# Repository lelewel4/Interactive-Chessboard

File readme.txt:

With my collegaues, I designed PCB to interactive chessboard.

The designed board should detect a given game piece on its field and, on this basis, send data to the microcontroller.
The microcontroller processes the data and determines the possible movements.
Depending on this, the board should glow with the appropriate LED color, e.g. red - a pawn to capture.

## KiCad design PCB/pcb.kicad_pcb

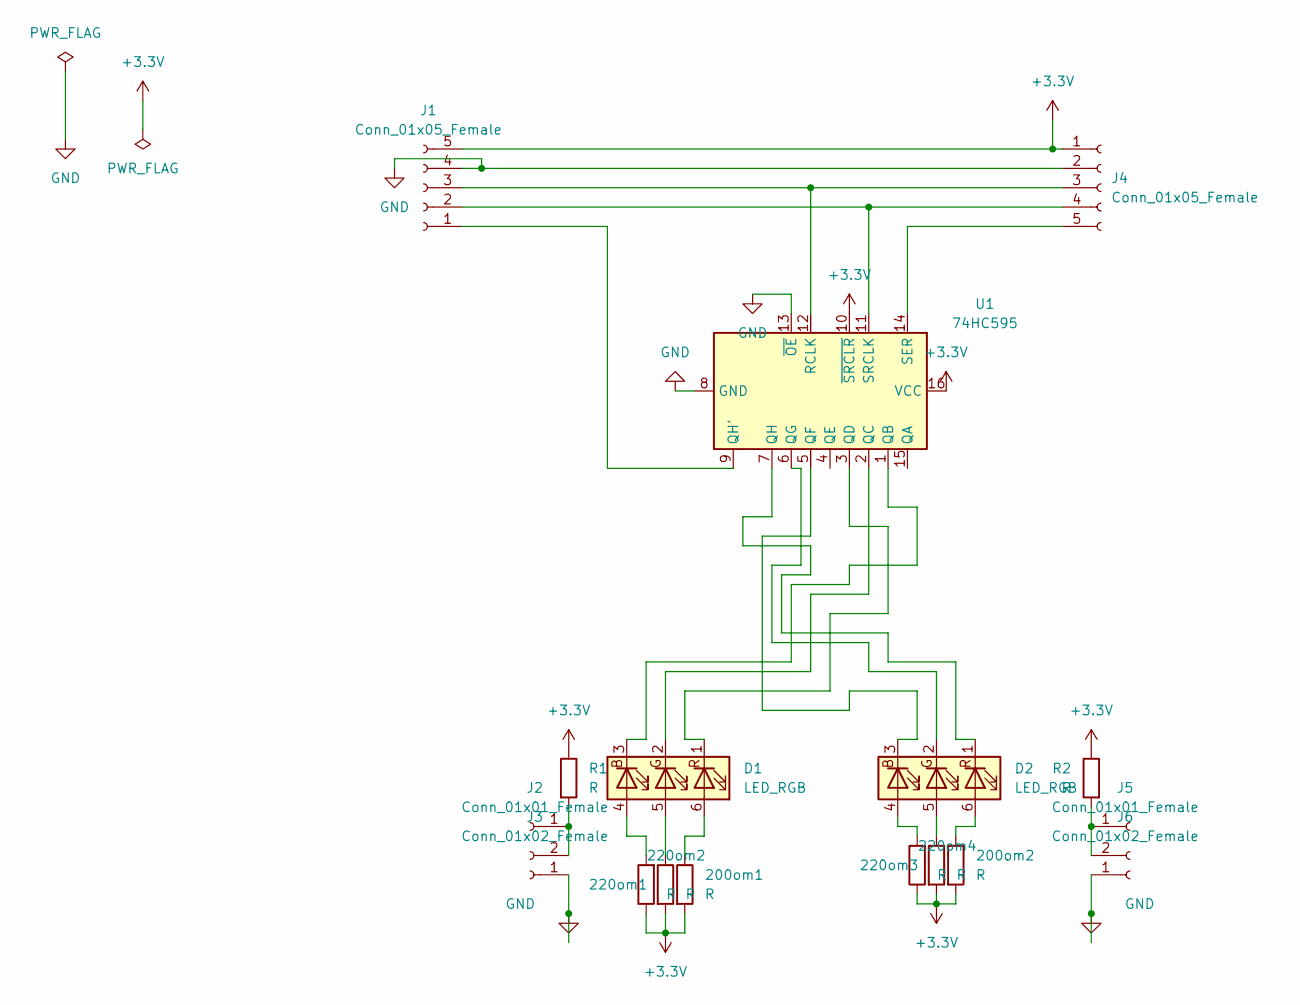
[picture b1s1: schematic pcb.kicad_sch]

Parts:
200om1, 200om2, 220om1, 220om2, 220om3, 220om4: R; R_0603_1608Metric_Pad0.98x0.95mm_HandSolder
D1, D2: LED_RGB; LED_RGB_PLCC-6
J1, J4: Conn_01x05_Female; PinHeader_1x05_P2.54mm_Vertical
J2, J5: Conn_01x01_Female; PinHeader_1x01_P2.54mm_Vertical
J3, J6: Conn_01x02_Female; PinHeader_1x02_P2.54mm_Vertical
R1, R2: R; R_0603_1608Metric_Pad0.98x0.95mm_HandSolder
U1: 74HC595; SO-16_3.9x9.9mm_P1.27mm

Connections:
+3V3: 200om1.2, 200om2.2, 220om1.1, 220om2.2, 220om3.1, 220om4.2, J1.5, J4.1, R1.1, R2.1, U1.10 (~SRCLR), U1.16 (VCC)
GND: J1.4, J3.1, J4.2, J6.1, U1.8 (GND), U1.13 (~OE)
unnamed: 200om1.1, D1.6 (RA)
unnamed: 200om2.1, D2.6 (RA)
unnamed: 220om1.2, D1.4 (BA)
unnamed: 220om2.1, D1.5 (GA)
unnamed: 220om3.2, D2.4 (BA)
unnamed: 220om4.1, D2.5 (GA)
unnamed: D2.1 (RK), U1.7 (QH)
unnamed: D2.3 (BK), U1.5 (QF)
unnamed: J1.1, U1.9 (QH')
unnamed: J1.2, J4.4, U1.11 (SRCLK)
unnamed: J1.3, J4.3, U1.12 (RCLK)
unnamed: J2.1, J3.2, R1.2
unnamed: J4.5, U1.14 (SER)
unnamed: J5.1, J6.2, R2.2
unnamed: D1.3 (BK), U1.1 (QB)
unnamed: D1.2 (GK), U1.2 (QC)
unnamed: D1.1 (RK), U1.3 (QD)
unnamed: D2.2 (GK), U1.6 (QG)

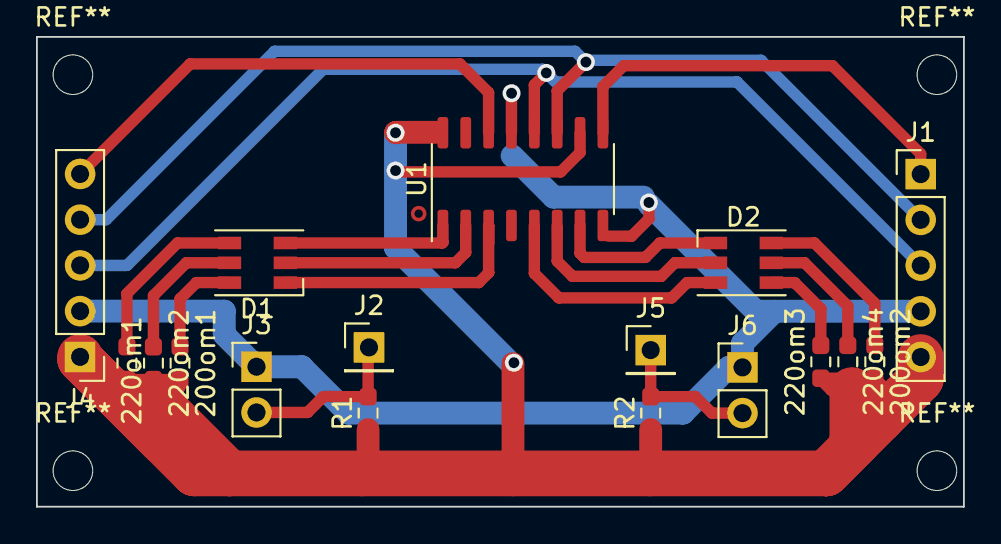
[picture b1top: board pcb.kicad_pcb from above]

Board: 2 copper layers, 51.5 x 26.1 mm, 17 parts (0 on the bottom side), 20 nets.

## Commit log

2023-10-08 Added to GIT
